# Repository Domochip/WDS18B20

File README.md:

# WDS18B20

This project allows you to build a wide DS18B20 sensors network **over a house**  
It uses :  

- a D1 Mini (ESP8266)
- some DS18B20 sensors
- a customized Tasmota firmware

## Build your 1-Wire bus

In order to get a wide 1-Wire bus (one that cover a house), Dallas provides some recommendations into their application note AN148.

This project use the Improved Interface bellow that is able to support a **200 meters long bus**:

This one requires a pin for reading the bus state and another one as output to drive the bus low : I named it the "Dual Pin OneWire"

**Warning : If you build a large 1 Wire bus inside your house, keep in mind that some voltage may appear on this one by induction. You need to have a good knowledge about electricity and associated risks!!!**

## Build your WDS18B20

All files are inside `schematic` subfolder and has been designed with KiCad

### Schematic

### PCB

### Print your box

Box project (Fusion 360) and STL files can be found into `box` folder

## Code/Compile/Flash

A specific variation in the Tasmota code needs to be done before compilation.  
**Compile it yourself** by following bellow steps **OR precompiled binaries are available in Releases**.

### Prepare compilation environment

You need to follow Tasmota guides to be ready for compilation:  
<https://tasmota.github.io/docs/Compile-your-build/>

### Code

You need to edit `tasmota/tasmota_xsns_sensor/xsns_05_ds18x20.ino` file

1. enable `#define DS18x20_USE_ID_AS_NAME` by removing the '//'
2. replace `#define DS18X20_MAX_SENSORS  8` by `#define DS18X20_MAX_SENSORS  16`
3. For PCB 3.0 and lower
   1. replace all `digitalWrite(DS18X20Data.pin_out, HIGH);` by `digitalWrite(DS18X20Data.pin_out, newLOW);`
   2. replace all `digitalWrite(DS18X20Data.pin_out, LOW);` by `digitalWrite(DS18X20Data.pin_out, HIGH);`
   3. replace all `digitalWrite(DS18X20Data.pin_out, newLOW);` by `digitalWrite(DS18X20Data.pin_out, LOW);`
4. save
5. Compile Tasmota
6. Rename resulting tasmota.bin to tasmota-WDS18B20-12.1.0.bin

### Flash

You will find all available tools to flash tasmota in the official documentation:  
<https://tasmota.github.io/docs/Getting-Started/#needed-software>

## Run

### Tasmota Configuration

You need to apply this Template:  
`{"NAME":"WDS18B20","GPIO":[0,0,0,0,0,0,0,0,1344,0,1312,0,0,0],"FLAG":0,"BASE":18,"CMND":"Module 0|TelePeriod 60"}`

To change number of digit after the dot on reported temperatures:  
`TempRes 2`

To Enable arithmetic mean over teleperiod:  
`SetOption126 1`

For more details, please refer to the Tasmota documentation:  
<https://tasmota.github.io/docs/DS18x20>

## And finally

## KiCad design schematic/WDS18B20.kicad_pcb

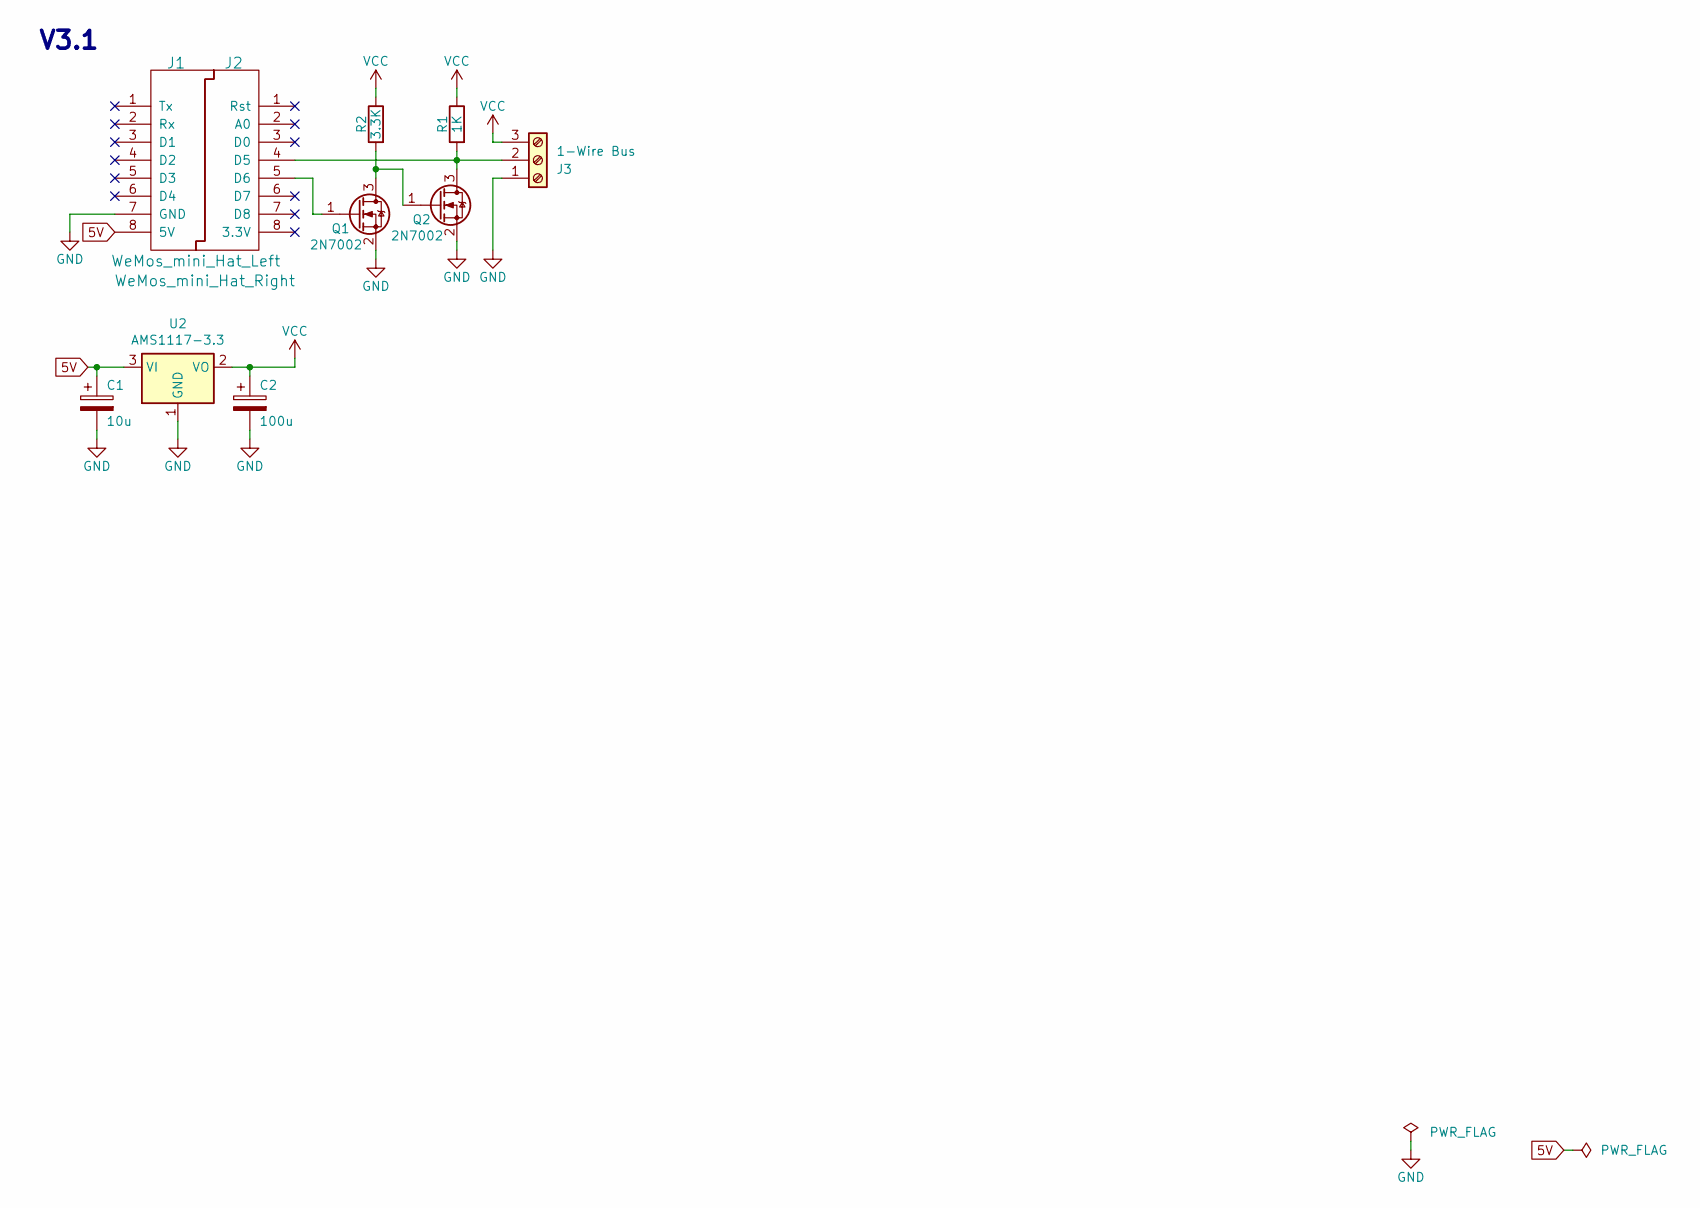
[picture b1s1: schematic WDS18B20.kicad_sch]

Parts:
C1: 10u; CP_EIA-3216-18_Kemet-A_Pad1.58x1.35mm_HandSolder; LCSC C7171
C2: 100u; CP_EIA-3528-21_Kemet-B_Pad1.50x2.35mm_HandSolder; LCSC C16133
J1: WeMos_mini_Hat_Left; WeMos_D1_mini_Hat_Left; LCSC C7509515
J2: WeMos_mini_Hat_Right; WeMos_D1_mini_Hat_Right; LCSC C7509515
J3: 1-Wire Bus; TerminalBlock_bornier-3_P5.08mm; LCSC C474882
Q1, Q2: 2N7002; SOT-23_Handsoldering; LCSC C8545
R1: 1K; R_0805_2012Metric_Pad1.20x1.40mm_HandSolder; LCSC C17513
R2: 3.3K; R_0805_2012Metric_Pad1.20x1.40mm_HandSolder; LCSC C26010
U2: AMS1117-3.3; SOT-223-3_TabPin2; LCSC C6186

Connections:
5V: C1.1, J1.8 (5V), U2.3 (VI)
GND: C1.2, C2.2, J1.7 (GND), J3.1, Q1.2 (S), Q2.2 (S), U2.1 (GND)
unnamed: J2.4 (D5), J3.2, Q2.3 (D), R1.2
unnamed: J2.5 (D6), Q1.1 (G)
unnamed: Q1.3 (D), Q2.1 (G), R2.2
VCC: C2.1, J3.3, R1.1, R2.1, U2.2 (VO)

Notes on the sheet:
V3.1

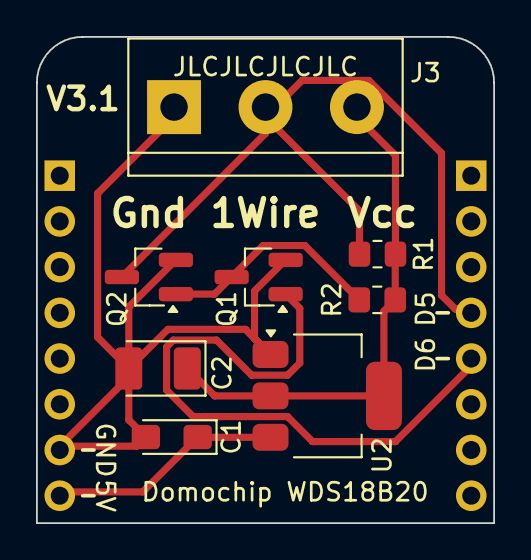
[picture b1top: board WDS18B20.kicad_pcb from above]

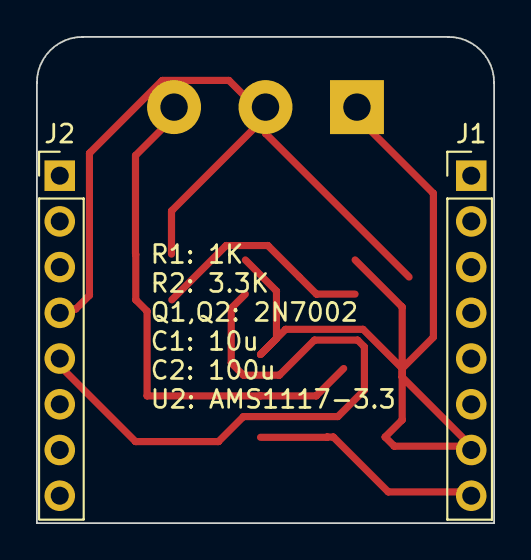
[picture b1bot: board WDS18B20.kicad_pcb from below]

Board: 2 copper layers, 25.4 x 27.0 mm, 10 parts (2 on the bottom side), 6 nets.

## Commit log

2017-11-26 Add Schematic and Box
2017-12-03 Switch Web Pages to new PureCSS design
2017-12-03 v3.1.2 More control on Config Webpage
2017-12-03 v3.1.3 Improve Status WebPage
2018-03-13 V3.1.4 Base Code Separated
2018-03-30 restore README
2018-04-15 V3.2.1 Add MQTT and Improve Convert
    Add MQTT protocol to upload temperature regularly
    Temperature Conversion changed to a scheduled (timer in loop) system
2018-05-22 Switch to PlatfromIO
2018-05-26 Add Base
2018-06-20 Switch to Base V1.0.10
2018-06-20 V3.2.2 BugFix
2018-06-20 Add rename script to PlatformIO
2018-10-26 Switch to Base V1.1.5
2018-11-17 Switch to Base V1.1.6
    - No More PowerShell
    - GZIP and convertion to header done in python with platformIO
    - Webpages small improvement
2018-11-27 Fix base
2019-03-17 V3.2.4 Switch to D1 Mini !!! Support only one OneWire bus Upgrade to Base V1.1.7
2019-03-17 Switch schematic to D1 Mini
2019-03-17 Change box for D1 Mini (Use Fusion 360)
2019-03-26 V3.2.5 Update to Base V1.2.0 Remove jQuery
2019-03-26 Fix Pure CSS - 1
2019-03-26 Fix Pure CSS - 2
2019-03-26 Update Box - Add 1Wire indications
2019-03-30 V3.2.6 Update to base V1.2.1
2019-03-31 V3.2.7 Update to base V1.2.2 Improve WiFi management
2019-04-06 Add box in STL format
2019-04-06 V3.3.0 Use Ticker instead of SimpleTimer Better MQTT management Better feedback of MQTT connection state Add library dependencies Update to base V1.2.4
2019-04-07 PureCSS Fix because of GIT AutoCRLF Windows users enable autocrlf by default, and so pure-min.css crlf modified make bad integrity check
2019-04-07 Fix MQTT Timed Out MQTT gave Timed Out state then no reconnection occured
2019-04-08 Add default MqttCallback
2019-04-08 Improved copy_base.py
2019-04-08 Improved javascript post function
2019-04-10 V3.3.1 BugFix MQTT reconnection
2019-04-11 V3.3.2 Improved Webpages to isolate contents
2019-04-13 Fix Webpage
2019-04-13 Minor improvement
2019-04-22 V3.3.3 no TLS for MQTT Update to Base V1.2.6
2019-08-12 Update gitignore
2019-10-13 Compatibility with Python3
2019-10-13 Minor improvments
2019-11-09 Up to Base V1.2.8
2019-11-15 Up to base V1.3.0
2019-11-17 Up to Base V1.3.1
2019-11-17 Base fix
2019-11-18 Up to Base V1.3.2
2019-11-22 Up to base V1.3.3
2019-11-23 Naming Convention
2019-11-23 V3.3.4 Add EventSource on status page
2019-11-26 Log AP Name
2019-11-26 small improvement on status page
2019-12-05 Improve status1.html
2019-12-05 Improve LOG_SERIAL
2020-01-07 Base Improvement LOG_SERIAL
2020-01-07 Update schematic - add Optional power for large network
2020-01-12 Update schematic
2020-02-01 fix info in config webpage
2020-11-01 Up to base V1.4.0 /!\ Configuration lost after flash /!\
2022-08-19 remove firmware
2022-08-19 Remove Jeedom chapter
2022-08-19 remove previous firmware doc
2024-07-28 Update pcb
2024-07-28 replace jpg with png
2024-10-19 Update schematic to KiCAD8
2024-10-19 Add KiCad gitignore
2024-10-19 Remove useless footprints
2024-10-19 Update wemos D1 mini footprint
2024-10-19 Add PWR_FLAG to schematic
2024-10-19 Update wemos courtyard
2024-10-19 V3.0 of the PCB (additional power is not optional)
2024-10-19 Update of schematic
2024-11-03 Update README images
2024-11-03 Update img
2024-11-05 Update schematic and PCB
2024-11-05 Update schematic and pcb images
2024-11-05 Improve footprints
2024-11-06 Rename KiCad Project
2024-11-09 New Box
2024-11-11 Update box
2024-11-11 Update box img
2024-11-24 Fix Lid terminal block offset
